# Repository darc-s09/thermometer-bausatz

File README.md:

# Bausatz LED-Thermometer

Dieser Bausatz beinhaltet ein LED-Thermometer mit 11 LEDs, die in
einem Halbkreis angeordnet sind.

Der Bausatz wird auf öffentlichen Veranstaltungen durch Interessenten
aufgebaut. Die Auswahl und Anordnung der verwendeten LEDs kann dabei
nach eigenem Geschmack selbst festlegt werden. Dafür wird ein kleiner
Steckbrett-Adapter verwendet, der statt der LEDs 11 2polige Fassungen
enthält und auf dem eine spezielle Demo-Firmware läuft.

Die gesamte Elektronik wird durch einen AVR-Mikrocontroller
realisiert. Außer dem Controller und den LEDs sind lediglich noch
ein Kondensator von 100 nF sowie zwei Jumper für Justage und die
Einstellung des Temperaturbereichs aufzulöten.

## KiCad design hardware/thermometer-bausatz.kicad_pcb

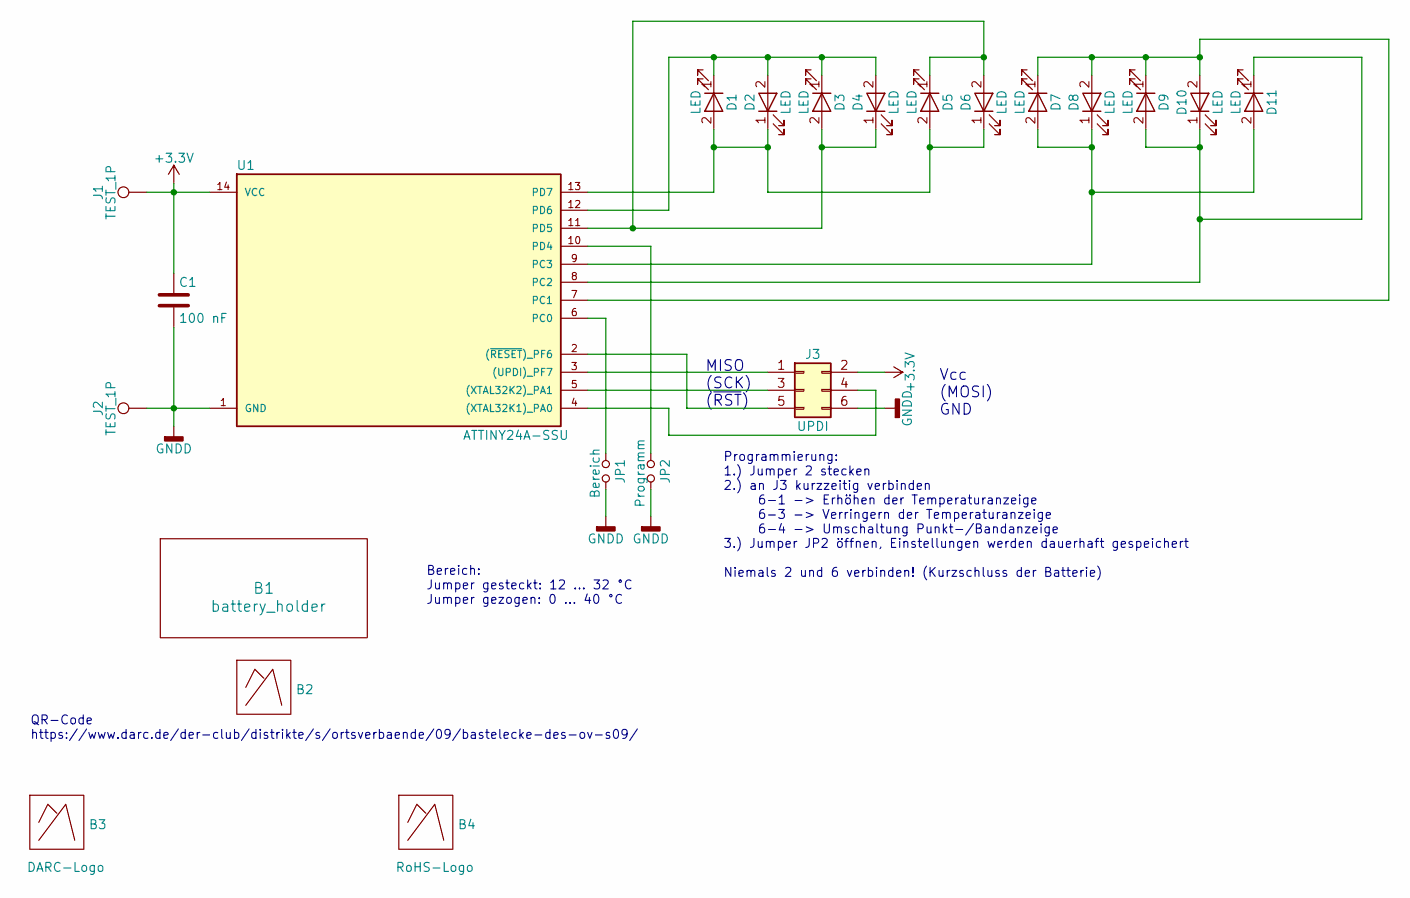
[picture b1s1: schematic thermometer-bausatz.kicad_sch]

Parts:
B1: battery_holder; Battery_holder_2xAAA
B2: bastelecke-url
B3: DARC-Logo; DARC-Raute
B4: RoHS-Logo; RoHS_Silk
C1: 100 nF; C_0805_2012Metric_Pad1.18x1.45mm_HandSolder
D1, D2, D3, D4, D5, D6, D7, D8, D9, D10, D11: LED; LED_D3.0mm
J1, J2: TEST_1P; TestPoint_THTPad_D3.0mm_Drill1.5mm
J3: UPDI; PinHeader_2x03_P2.54mm_Vertical
JP1: Bereich; JP2-SMD
JP2: Programm; JP2-SMD
U1: ATTINY24A-SSU; SOIC-14_3.9x8.7mm_P1.27mm

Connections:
+3V3: C1.1, J1.1, J3.2, U1.14 (VCC)
GNDD: C1.2, J2.1, J3.6, JP1.2, JP2.2, U1.1 (GND)
unnamed: D1.2 (A), D2.1 (K), D5.2 (A), D6.1 (K), U1.13 (PD7)
unnamed: D1.1 (K), D2.2 (A), D3.1 (K), D4.2 (A), U1.12 (PD6)
unnamed: D3.2 (A), D4.1 (K), D5.1 (K), D6.2 (A), U1.11 (PD5)
unnamed: D7.1 (K), D8.2 (A), D9.1 (K), D10.2 (A), U1.7 (PC1)
unnamed: D9.2 (A), D10.1 (K), D11.1 (K), U1.8 (PC2)
unnamed: D7.2 (A), D8.1 (K), D11.2 (A), U1.9 (PC3)
unnamed: J3.1, U1.3 ((UPDI)_PF7)
unnamed: J3.3, U1.5 ((XTAL32K2)_PA1)
unnamed: J3.4, U1.4 ((XTAL32K1)_PA0)
unnamed: J3.5, U1.2 ((~RESET)_PF6)
unnamed: JP1.1, U1.6 (PC0)
unnamed: JP2.1, U1.10 (PD4)

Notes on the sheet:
QR-Code https://www.darc.de/der-club/distrikte/s/ortsverbaende/09/bastelecke-des-ov-s09/
Vcc (MOSI) GND
Programmierung: 1.) Jumper 2 stecken 2.) an J3 kurzzeitig verbinden 6-1 -> Erhöhen der Temperaturanzeige 6-3 -> Verringern der Temperaturanzeige 6-4 -> Umschaltung Punkt-/Bandanzeige 3.) Jumper JP2 öffnen, Einstellungen werden dauerhaft gespeichert Niemals 2 und 6 verbinden! (Kurzschluss der Batter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
MISO (SCK) (~{RST})
Bereich: Jumper gesteckt: 12 … 32 °C Jumper gezogen: 0 … 40 °C

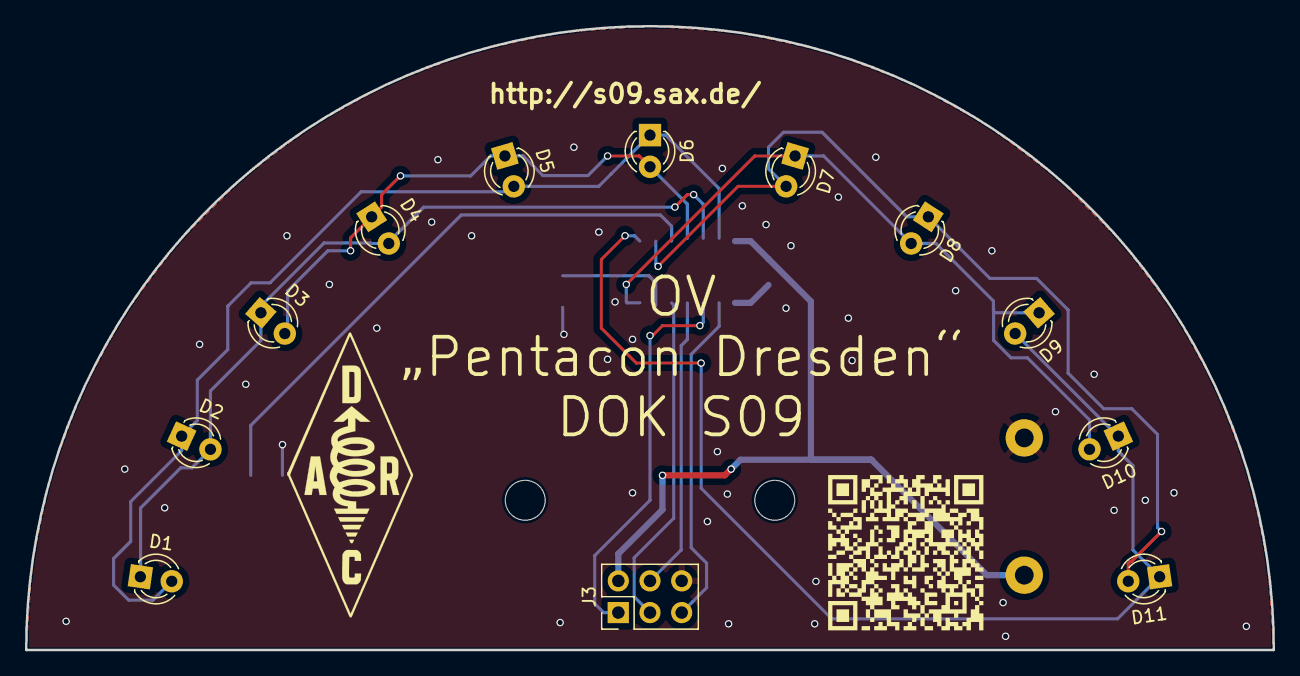
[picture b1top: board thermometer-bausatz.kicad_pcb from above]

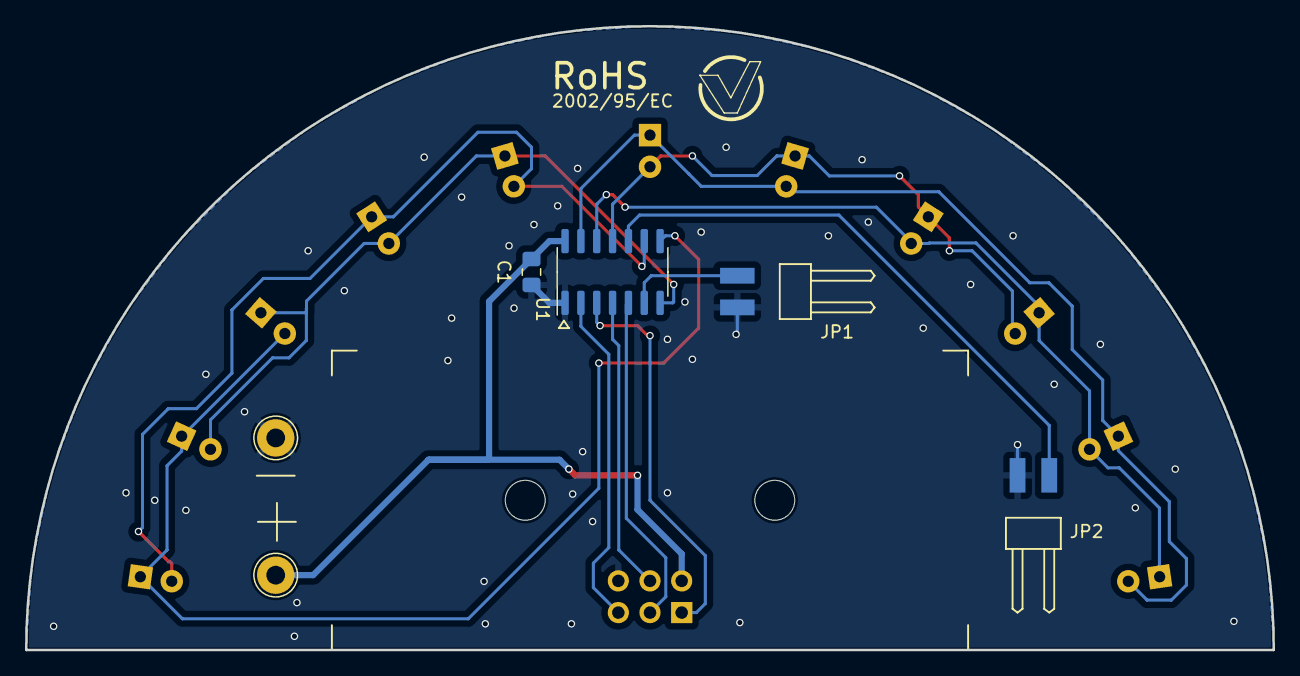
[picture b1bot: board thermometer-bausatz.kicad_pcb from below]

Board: 2 copper layers, 100.0 x 50.0 mm, 22 parts (8 on the bottom side), 14 nets.

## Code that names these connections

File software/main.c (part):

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        cycle = 0;
    }

    // LEDs are on PD7, PD6, PD5
    uint8_t port = PORTD.OUT & ~0b11100000; // preserve all non-LED bits,
    uint8_t ddr  = PORTD.DIR & ~0b11100000; // but mask LED bits to 0

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        /*
         * charlieplexing matrix lower LEDs
         *
         * LED1: PD7 high, PD6 low,  PD5 off
         * LED2: PD7 low,  PD6 high, PD5 off
         * LED3: PD7 off,  PD6 low,  PD5 high
         * LED4: PD7 off,  PD6 high, PD5 low
         * LED5: PD7 high, PD6 off,  PD5 low
         * LED6: PD7 low,  PD6 off,  PD5 high
         * off:  PD7 low,  PD6 low,  PD5 low
         */

        if (cycle == 0)      { ddr |= 0b11000000; port |= 0b10000000; }
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    PORTD.OUT = port;
    PORTD.DIR = ddr;

    // LEDs are on PC3, PC2, PC1
    port = PORTC.OUT & ~0b00001110;
    ddr  = PORTC.DIR & ~0b00001110;

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        /*
         * charlieplexing matrix upper LEDs
         *
         * LED7:  PC3 high, PC2 off,  PC1 low
         * LED8:  PC3 low,  PC2 off,  PC1 high
         * LED9:  PC3 off,  PC2 high, PC1 low
         * LED10: PC3 off,  PC2 low,  PC1 high
         * LED11: PC3 high, PC2 low,  PC1 off
         * LED12: PC3 low,  PC2 high, PC1 off  // not mounted
         * off:   PC3 low,  PC2 low,  PC1 low
         */
        if (cycle == 0)      { ddr |= 0b00001010; port |= 0b00001000; }
        else if (cycle == 1) { ddr |= 0b00001010; port |= 0b00000010; }
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static void
led_dim(void)
{
    // LEDs are on PD7, PD6, PD5
    if (leds[cycle] == DIM || leds[cycle] == DIM_FLASH)
    {
        PORTD.OUT &= ~0b11100000; // output low
        PORTD.DIR |=  0b11100000;
    }

    // LEDs are on PC3, PC2, PC1
    if (leds[cycle + NLEDS] == DIM || leds[cycle + NLEDS] == DIM_FLASH)
    {
        PORTC.OUT &= ~0b00001110; // output low
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    TCE0.INTCTRL = TCE_CMP0_bm | TCE_OVF_bm;  /* overflow and compare 0 interrupts */
    TCE0.CTRLA = TCE_ENABLE_bm;

    /* PD4: jumper 2 */
    /* PF7: UPDI */
    /* PA0/1: spare/adjust */
    /* PC0: jumper 1 */
    /* Enable pullups for all these pins */
    PORTD.PIN4CTRL = PORT_PULLUPEN_bm;
    PORTF.PIN7CTRL = PORT_PULLUPEN_bm;
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    PORTA.PIN1CTRL = PORT_PULLUPEN_bm;
    PORTC.PIN0CTRL = PORT_PULLUPEN_bm;

    /* LED group 1: PD7/6/5 */
    /* LED group 2: PC3/2/1 */

    /* ADC: internal 1.024 V reference, temperature sensor channel */
    ADC0.CTRLC = ADC_REFSEL_1V024_gc;
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
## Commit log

2018-06-19 First version with working Charliexplexing.
2018-06-19 add copyright
2018-06-19 Bump dimmed LED duty cycle to 1:10, and increase heartbeat to 3000 Hz.
2018-06-20 Try to implement temperature measurement.
2018-06-20 Add .hgignore file.
2018-06-20 Add USI UART example.
    Slightly over size for ATtiny24 now.
2018-06-20 Add USI UART (AVR307).
    Does not work yet.
2018-06-21 Actually turn USI DO into an output.
2018-06-21 Adapt code to use CTC rather than timer pre-seeding.
2018-06-22 Fork the early version out as test firmware. Just turns on all LEDs, some dimmed, some fully bright.
2018-06-25 Reduce duty cycle for dimmed LEDs, to improve contrast.
2018-06-26 Bump CPU clock to 8 MHz. Consequently, use prescaler 8 for timer0.
    Implement IO direction/pullup switching from AVR307 (just in case).
    Makes UART work.
2018-06-27 Implement basic stdio ADC value printout.
2018-06-27 Bump UART Tx buffer size to 16 (for printf()).
    Move printout code into the "new temperature value detected" part.
    Keep ADC enabled all the time.
    Now, it yields meaningful temperature readings.
2018-06-27 Make demo modus a real demo.
2018-06-27 Fix F_CPU in Makefile, adapt timing inside accordingly.
2018-06-28 Rewrite charlieplexing/dimming function to use "early off" dimming through OCR1B. Heavily reduces interrupt load.
2018-06-28 Commit current state as UART, to remove USI code from default branch.
2018-06-28 Remove USI UART code from default branch.
2018-06-29 Implement flash and flash-dim states.
2018-06-29 Use jumper 1 for range setting.
2018-06-29 Implement EEPROM data saving
2018-06-29 Implement actual calibration.
2018-06-29 Default programmer to AVRISPmkII.
2018-06-29 Add a lot of comments.
2022-06-16 Turn temperature calculation to integer
    While the datasheet mentions a correction coefficient of 0.996,
    the resulting error from ignoring it is not important given
    the coarse resolution of the LED display.
    Turning the calculations from float to integer easily allows
    the code to fit into an ATtiny24.
2022-09-11 Change programmer to AVRISPmkII
    Also add parameter for slower ISP clock.
2024-06-23 Make software subdir
2024-06-23 Check old Kicad files into git repository
    This is the state that has been used for the first hardware
    revision, June 2018.
2024-06-23 Upgrade to Kicad 7
    Upgrade project files.
    Schematics now ends in .kicad_sch rather .sch.
2024-06-23 Resolve DRC errors
2024-06-23 Add QR code for URL
2024-06-23 Modernize everything
2024-06-23 Add a gerbv configuration file
2024-06-23 Add local libraries
2024-06-23 Add a README file
    This will be displayed on Github.
2024-06-23 Remove old .hgignore file.
    That file was left over from the Mercurial migration.
2024-06-23 Add documentation
    This is basically the existing documentation from "Bastelecke",
    converted to markdown.
2024-06-26 Replace ATtiny24 by AVR16EB14
    While both controllers share the same footprint, the AVR16EB14
    is quite a bit different. To begin, the footprints have VDD and
    GND swapped. The AVRxEB uses UPDI for programming, so basically
    only a single wire is needed. The GPIOs are scattered across
    more ports. Finally, the entire clock system and ADC is
    different.
2024-06-26 Remove external temperature sensor
    The external sensor was initially designed as an option to allow for a
    more accurate temperature sensor. To save part costs, it has never
    actually been implemented.
    With the AVRxEB, the internal temperature sensor comes pre-calibrated
    (through fuse values), so it is safe to get rid of that idea
    entirely.
2024-06-27 Replace ATtiny24 by AVR16EB14
    While both controllers share the same footprint, the AVR16EB14
    is quite a bit different. To begin, the footprints have VDD and
    GND swapped. The AVRxEB uses UPDI for programming, so basically
    only a single wire is needed. The GPIOs are scattered across
    more ports. Finally, the entire clock system and ADC is
    different.
2024-06-27 Rename NDIM to DIM_DUTYCYCLE
2024-06-27 Use AtmelICE in UPDI mode as programmer
2024-06-27 Fix bit positions for LED outputs, fix timer interrupts
    LED bit positions were still at their old (ATtiny24) values.
    Timer interrupt flags need to be manually cleared on AVRxEB.
2024-06-27 CLKCTRL.MCLKCTRLB is configuration-change protected
    Setup CCP before modifying the system clock.
2024-06-28 Fix LED bit patterns
    Make the LED bit patterns actually match the schematics.
2024-06-29 Add UART debugging
    This is simpler than it used to be in the ATtiny24 before.
    PA0 is USART0.TxD which is conveniently free as one of the
    adjustment pins.
2024-06-29 Increase the ADC sample time
    With the recommended minimum sample time of 32 µs, the result
    was quite "jumpy". Increasing it to 64 µs yielded a stable
    conversion result.
2024-06-29 Fix typo: PC0 needs pullup, rather than PC1
2024-06-29 Fix temperature calculation: everything is in Kelvin
    The previous code already assumed a Kelvin temperature in
    the calculation, and initialized the offset to 275. Since
    the AVRxEB temperature sensor calculation natively yields
    Kelvin, just use that one throughout the code, but set
    the initial (unadjusted) offset to 273.
2024-06-29 Everyone's favorite: default to stripe mode
    During all sessions of the past 6 years, we noticed that stripe
    mode (rather than dot mode) is people's favorite, so use it.
2024-06-29 Increase ADC sample time to 100 µs
    Even 64 µs turned out to be not that stable.
2024-06-29 Clear ADC interrupt flag in ISR
2024-06-29 Actually enable the ADC when setting it up.
2024-07-14 Change MCU type to AVR16EB14-I/SL
2025-09-16 Fix polarity of calibration jumpers
    As the jumpers are low-active, their value must be negated
    before use.
